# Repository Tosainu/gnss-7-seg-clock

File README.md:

# GNSS Seven-segment Clock

GNSS-powered, seven-segment table clock.

https://github.com/user-attachments/assets/9b2d0560-d879-4ddb-b99d-07a6e9839360

Full video: https://www.youtube.com/watch?v=Y1P_iDvq4bk

## Firmware

### Usage

Pre-build firmware files are available on the [release page](https://github.com/Tosainu/gnss-7-seg-clock/releases). Thanks to the RP2040 Bootrom, flashing the firmware requires no special tool. Connect the board to the PC using the USB-C cable, while holding the BOOT button (`SW2`). Once the `RPI-RP2` drive appears on the PC, copy `gnss-7-seg-clock.uf2` there. The board will automatically be rebooted as soon as it finishes writing to Flash.

- The board displays `--.--.--` until it obtains the time information.
- Press `SW3` to change the display contents:
    1. Time: `hh.mm.ss`
    2. Date: `YY.MM.DD`
    3. Configuring time zone (time offset): `[-]hh.mm`
        - `SW4`: + 30 min
        - `SW5`: - 30 min

### Build

The firmware is written in the [Rust][rust] programming language with the [Embassy][embassy] framework. In order to build the firmware, you first need to prepare the Rust toolchain. Please refer to the [official guide][rustup].

Next, install the linker helper [`flip-link`][flip-link]. Alternatively, remove [this line](https://github.com/Tosainu/gnss-7-seg-clock/blob/446c9426d9386b7eddf7218308c7567423a233c5/.cargo/config.toml#L11) to use the default linker.

    $ cargo install --locked flip-link

Lastly, run the command below to build the firmware. You can find the ELF file `./target/thumbv6m-none-eabi/release/gnss-7-seg-clock` afterward.

    $ cargo build --release

If the debug probe is attached to the board and [probe-rs][probe-rs] is installed on your PC, `cargo run` can be used to load firmware to the board.

    $ cargo run --release
    
    # to run test apps in crates/gnss-7-seg-clock/examples/
    $ cargo run --release --example gnss-uart-pipe

## Schematic and PCB

> [!IMPORTANT]
> I'm new to circuits and PCB designs. Any feedback and advice are welcome! (✿ゝ◡╹)ノ

I designed the Rev.A board with KiCad v8.0.8 (Linux/macOS) and their official libraries. You can find the KiCad project files in the [`hardware/`](./hardware/) directory. You can also find the rendered schematic (PDF) and Gerber files on the [release page](https://github.com/Tosainu/gnss-7-seg-clock/releases/tag/hardware%2Frev-a).

<sub>
Please do not take a close look at 43-44 pins of RP2040! (ignorable solder bridge)
</sub>

### Parts

> [!NOTE]
> Tolerances were set by just referring to several existing designs. Some of them might be insufficient or overkill.

| Reference | Value | Parts | Qty |
| --- | --- | --- | --: |
| `C1`, `C2`, `C4-C10`, `C14`, `C17-C19` | MLCC, 0.1uF, 10%, 6.3V, X5R, M1005 | | 13 |
| `C3`, `C11` | MLCC, 1uF, 20%, 6.3V, X5R, M1005 | | 2 |
| [`C12`, `C13`](#ldo-and-capacitors) | MLCC, 10uF, 10%, 6.3V, X7R, M2012 | | 2 |
| `C15`, `C16` | MLCC, 15pF, 5%, 50V, C0G/NP0, M1005 | | 2 |
| [`C20`](#rf-circuitry-for-max-m10s) | MLCC, 10000pF, 10%, 16V, X7R, M1005 | | 1 |
| [`C21`](#rf-circuitry-for-max-m10s) | MLCC, 47pF, 5%, 50V, C0G/NP0, M1005 | | 1 |
| [`D1`](#rf-circuitry-for-max-m10s) | Bidirectional TVS, M1005 | [Littelfuse PESD0402-140][PESD0402-140] | 1 |
| `D2-D7` | LED, M1005 | | 6 |
| `J1` | USB-C Receptacle | [GCT USB4105-GF-A](https://gct.co/connector/usb4105) | 1 |
| `J2` | SMA Receptacle, Edge Mount | [Molex 732511153][732511153] | 1 |
| `J3` | Pin header, 01x03, P2.54 mm | | 1 |
| [`L1`](#rf-circuitry-for-max-m10s) | Inductor, 27nH, 5%, M1005 | [Murata LQG15HS27NJ02D][LQG15HS27NJ02D] | 1 |
| [`R1-R3`](#driving-seven-segment-leds-with-fewer-pins) | Resistor, 2.2kOhm, 1%, 1/16W, M1005 | | 3 |
| `R4`, `R5`, `R12`, `R14-R16` | Resistor, 10kOhm, 1%, 1/16W, M1005 | | 6 |
| `R6`, `R7` | Resistor, 5.1kOhm, 1%, 1/16W, M1005 | | 2 |
| `R8`, `R9` | Resistor, 27Ohm, 1%, 1/16W, M1005 | | 2 |
| `R10`, `R13` | Resistor, 1kOhm, 1%, 1/16W, M1005 | | 2 |
| [`R11`](#rf-circuitry-for-max-m10s) | Resistor, 10Ohm, 5%, 1/4W, M1005 | | 1 |
| `R17-R22` | Resistor, 470Ohm, 1%, 1/16W, M1005 | | 6 |
| `SW1-SW5` | Tactile Switch | [C&K PTS810][PTS810] | 5 |
| [`U1-U6`](#seven-segment-leds) | 7-segment LED, Common-Anode, 3.81 mm | | 6 |
| [`U7-U9`](#driving-seven-segment-leds-with-fewer-pins) | 16-ch LED sink driver, SOIC-24W | [TI TLC5925IDWR][TLC5925] | 3 |
| `U10` | MCU | [Raspberry Pi RP2040][RP2040] | 1 |
| [`U11`](#ldo-and-capacitors) | LDO, 3.3V, 500 mA, SOT-23-5 | [TI TLV75533PDBVR][TLV755P] | 1 |
| `U12` | SQPI NOR Flash, 32M-bit, SOIC-8 | [Winbond W25Q32JVSS][W25Q32JV] | 1 |
| `U13` | GNSS Receiver | [u-blox MAX-M10S][MAX-M10] | 1 |
| `Y1` | Crystal, 12MHz | [Abracon ABM8-272-T3][ABM8-272-T3] | 1 |
| | GNSS Active Antenna | [u-blox ANN-MB5][ANN-MB5] | 1 |

### Seven-segment LEDs

`U1-U6` are seven-segment LEDs, the essential components in this design. While selecting them, I was surprised about the poor availability of seven-segment LEDs, especially the larger models (> 1″). I wanted to use [Kingbright SA15-11GWA][SA15-11GWA] initially. However, due to the availability and price, I selected [WENRUN LSD150BAG-101][LSD150BAG-101], even though I had to use a different store from other parts.

Unfortunately, LSD150BAG-101 is not a drop-in replacement for SA15-11GWA. They have a different pitch for the vertical direction: 40.64mm (SA15-11GWA) and 40.00mm (LSD150BAG-101). Since I wanted to have some flexibility in the design, I made the footprint that uses the oval pad so that can use both types of seven-segment LEDs.

The forward voltage also has to be taken into account for `U1-U6`. Vf should be smaller than the USB VBUS. For instance, high-luminance types are not suitable in general.

### Driving Seven-segment LEDs with Fewer Pins

`U7`, `U8`, and `U9` are 16-ch shift registers specialized for the LED, [TI TLC5925IDWR](TLC5925). Thanks to this three-cascading configuration, it can drive six seven-segment LEDs (48x LED segments) only by five pins.

TLC5925 determines the output currents based on an external resistor between the `R-EXT` pin and `GND`. `R1`, `R2`, and `R3` are the current-set resistors for `U7`, `U8`, and `U9` respectively. With the 2.2kOhm resistor, the output would be (1.21 / 2,200) \* 18  = 9.9mA.

### LDO and Capacitors

`U11` is the 3.3V LDO, [TI TLV75533PDBVR](TLV755P) (TLV755P-series). I'm hoping it works nicely with an AC adapter/wall charger as well as a PC because of its good PSRR in wide-range frequencies.

`C12` and `C13` are the input and output capacitors for the LDO. According to the datasheet, TLV755P requires a 1uF+ input capacitor and a 0.47uF+ output capacitor while considering the DC bias characteristics of a capacitor. Based on this, I selected 10uF/6.3V MLCC.

### RF Circuitry for MAX-M10S

[sparkfun/SparkFun\_u-blox\_MAX-M10S][SparkFun-MAX-M10S] is very good material as well as the MAX-M10S Integration manual. For the RF part, I imitated SparkFun's board and filled in parts values based on the reference design mentioned in the integration manual. Here are the parts correspondences between this board and the MAX-M10S reference design:

| This board | Reference design | Use |
| --- | --- | --- |
| `C20` | `C14` |  RF Bias-T Capacitor |
| `C21` | `C18` | DC Block Capacitor[^dc-block-cap] |
| `L1` | `L3` | RF Bias-T Inductor |
| `R11` | `R8` | Antenna supervisor current limiter/shunt resistor |

`D1` is the ESD-protection TVS which is only in the SparkFun's board. Since I have no confidence in finding compatible parts, I used the same TVS [Littelfuse PESD0402-140][PESD0402-140] in this design.

[^dc-block-cap]: Apparently, this capacitor can be removed as my design doesn't have an external SAW filter. The built-in DC-block capacitor of the module is sufficient.

## Special Thanks - PCBWay

I would like to say a special thank you to [PCBWay](https://www.pcbway.com/) for reaching out and sponsoring my project. As part of the sponsorship, I had the opportunity to try their PCBA service. Overall I am very satisfied with the service and quality of the PCBs. Especially,

- Swift and kind support
    - I was surprised that they reviewed my design files very quickly and gave me a reply after about an hour from the order.
- Numerous customization options for PCB manufacturing
- Help Center
    - There are how-to specialized for KiCad such as [_"How to Generate Gerber and Drill Files in KiCad 8.0?"_](https://www.pcbway.com/helpcenter/generate_gerber/Generate_Gerber_file_from_Kicad.html) and [_"Generate Position File Centroid File(pick place) in Kicad"_](https://www.pcbway.com/helpcenter/design_instruction/Generate_Position_File_in_Kicad.html). They were very helpful when I generate design files for the order.
- Quality of PCBs
    - The board has RP2040 which is the 0.20 mm pitch IC but there were no major issues. One thing to note is the soldermask color: green would be the only choice for such boards according to their explanations and the document [_"Soldermask Issues - Soldermask bridge"_](https://www.pcbway.com/helpcenter/soldermask_issues/Soldermask_bridge.html).

Note that I made some changes from the Rev.A design for this order, such as changing footprints to a non-HandSolder variant. If you're interested in about the design files I used to order, please refer to the [Rev.A2 release](https://github.com/Tosainu/gnss-7-seg-clock/releases/tag/hardware%2Frev-a2).

## License

The project is licensed under the [MIT](./LICENSE) license unless otherwise stated.

PCD design files, specifically the files under the [`hardware/`](./hardware/) directory are licensed under the [CC BY-SA 4.0](https://creativecommons.org/licenses/by-sa/4.0/) license. Please note that:
- Footprint files described below are made based on the [KiCad Footprint Libraries](https://gitlab.com/kicad/libraries/kicad-footprints) which is licensed under the [CC-BY-SA 4.0 license with exceptions](https://gitlab.com/kicad/libraries/kicad-footprints/-/blob/8.0.8/LICENSE.md?ref_type=tags).
    - [`Display_7Segment_1.5inch_P2.45mm.kicad_mod`](./hardware/gnss-7-seg-clock.pretty/Display_7Segment_1.5inch_P2.45mm.kicad_mod)
    - [`QFN-56-1EP_7x7mm_P0.4mm_EP3.2x3.2mm_HandSolder.kicad_mod`](./hardware/gnss-7-seg-clock.pretty/QFN-56-1EP_7x7mm_P0.4mm_EP3.2x3.2mm_HandSolder.kicad_mod)
    - [`SW_SPST_PTS810_HandSolder.kicad_mod`](./hardware/gnss-7-seg-clock.pretty/SW_SPST_PTS810_HandSolder.kicad_mod)
    - [`USB_C_Receptacle_GCT_USB4105-xx-A_16P_TopMnt_Horizontal_HandSolder.kicad_mod`](./hardware/gnss-7-seg-clock.pretty/USB_C_Receptacle_GCT_USB4105-xx-A_16P_TopMnt_Horizontal_HandSolder.kicad_mod)
- 3D model of ublox MAX module [`MAX (STEP-AP214).STEP`](./hardware/3d_models/MAX%20(STEP-AP214).STEP) is copied from [u-blox/3D-Step-Models-Library@92ce6ba0](https://github.com/u-blox/3D-Step-Models-Library/tree/92ce6ba04a1dacdbec4c5b9e0c032d87bb4d9fc0).

    > Copyright (C) u-blox
    >
    > u-blox reserves all rights in this deliverable (documentation, software, etc., hereafter “Deliverable”).
    >
    > u-blox grants you the right to use, copy, modify and distribute the Deliverable provided hereunder for any purpose without fee.
    >
    > THIS DELIVERABLE IS BEING PROVIDED "AS IS", WITHOUT ANY EXPRESS OR IMPLIED WARRANTY. IN PARTICULAR, NEITHER THE AUTHOR NOR U-BLOX MAKES ANY REPRESENTATION OR WARRANTY OF ANY KIND CONCERNING THE MERCHANTABILITY OF THIS DELIVERABLE OR ITS FITNESS FOR ANY PARTICULAR PURPOSE.
    >
    > In case you provide us a feedback or make a contribution in the form of a further development of the Deliverable (“Contribution”), u-blox will have the same rights as granted to you, namely to use, copy, modify and distribute the Contribution provided to us for any purpose without fee.

- Circuits around the MAX-M10S module on the schematic are made based on [sparkfun/SparkFun\_u-blox\_MAX-M10S][SparkFun-MAX-M10S] which is licensed under the [CC BY-SA 4.0](https://github.com/sparkfun/SparkFun_u-blox_MAX-M10S/blob/8e937406ba0f21e3afc8ca20ddeb06b088023951/LICENSE.md#hardware) license for the hardware part.

This project is inspired by [Kello version 4](http://kair.us/projects/clock/v4/index.html).

[rust]: https://www.rust-lang.org/
[rustup]: https://www.rust-lang.org/tools/install
[embassy]: https://embassy.dev/
[flip-link]: https://github.com/knurling-rs/flip-link
[probe-rs]: https://probe.rs/

[RP2040]: https://www.raspberrypi.com/products/rp2040/
[LQG15HS27NJ02D]: https://www.murata.com/en-global/products/productdetail?partno=LQG15HS27NJ02%23
[LSD150BAG-101]: https://www.tme.eu/en/details/lsd150bag-101/7-segment-led-displays/wenrun/lsd150bag-101-01/
[PESD0402-140]: https://www.littelfuse.com/products/overvoltage-protection/polymer-esd-suppressors/pesd-protection-device/pesd/pesd0402-140
[PTS810]: https://www.ckswitches.com/products/switches/product-details/Tactile/PTS810/
[TLC5925]: https://www.ti.com/product/TLC5925
[TLV755P]: https://www.ti.com/product/TLV755P
[W25Q32JV]: https://www.winbond.com/hq/product/code-storage-flash-memory/serial-nor-flash/?__locale=en&partNo=W25Q32JV
[732511153]: https://www.molex.com/en-us/products/part-detail/732511153
[USB4105]: https://gct.co/connector/usb4105
[ABM8-272-T3]: https://abracon.com/datasheets/ABM8-272-T3.pdf
[ANN-MB5]: https://www.u-blox.com/en/product/ann-mb5-antenna
[MAX-M10]: https://www.u-blox.com/en/product/max-m10-series
[SA15-11GWA]: https://www.kingbrightusa.com/product.asp?catalog_name=LED&product_id=SA15-11GWA

[SparkFun-MAX-M10S]: https://github.com/sparkfun/SparkFun_u-blox_MAX-M10S

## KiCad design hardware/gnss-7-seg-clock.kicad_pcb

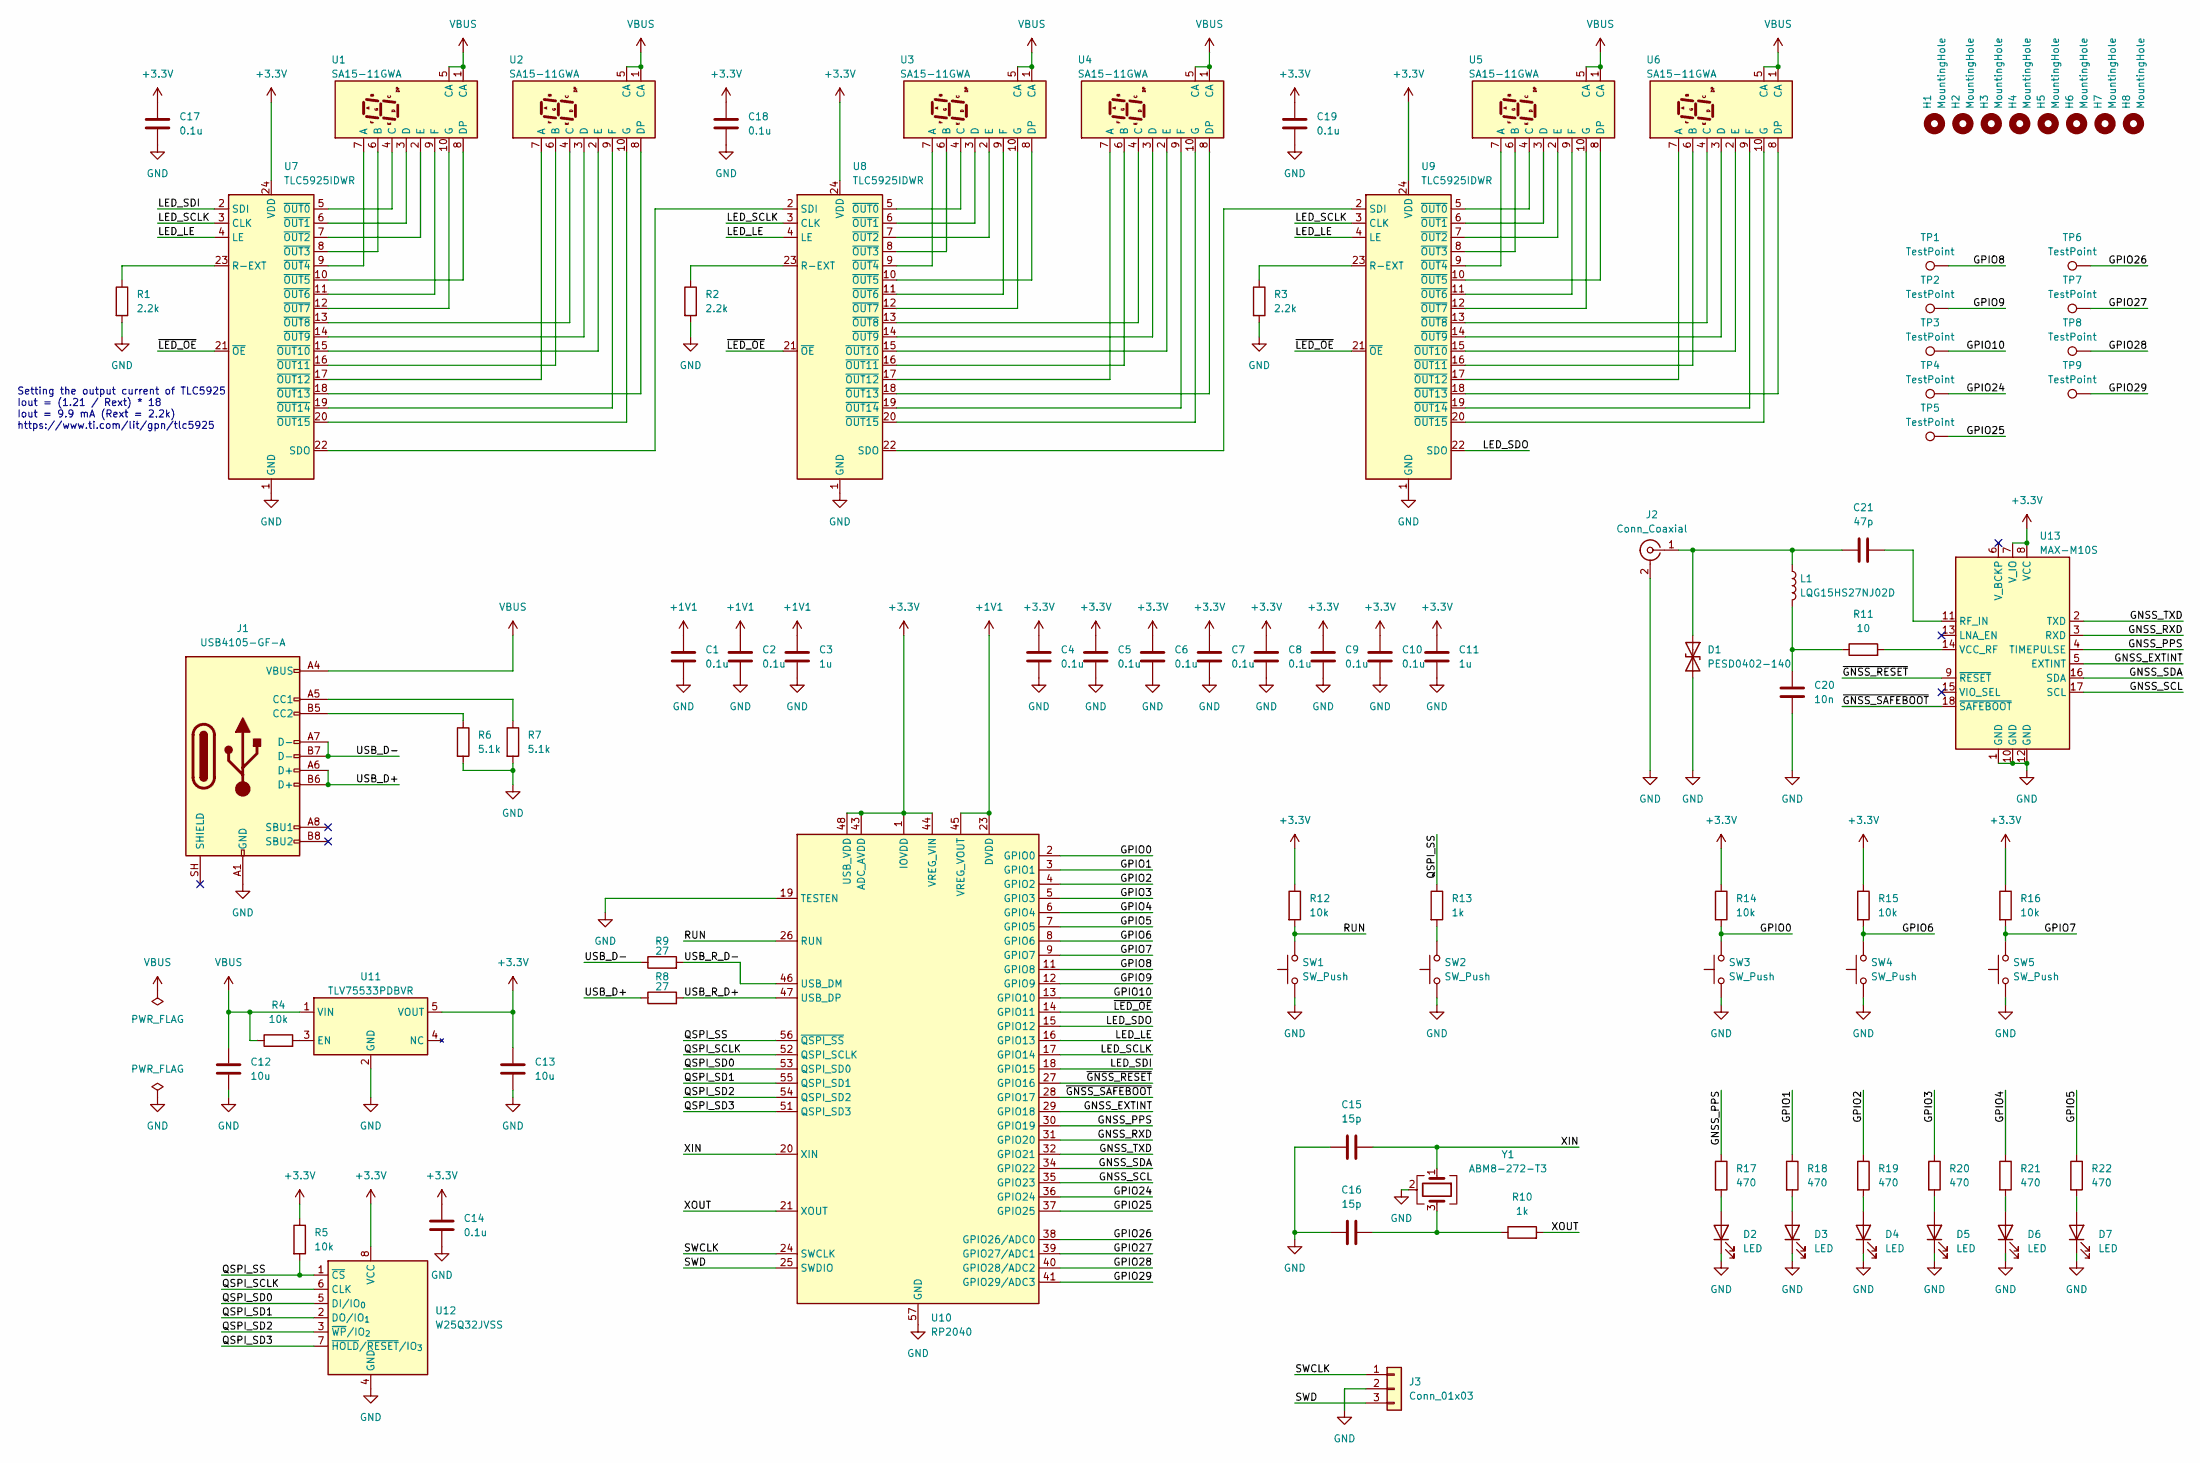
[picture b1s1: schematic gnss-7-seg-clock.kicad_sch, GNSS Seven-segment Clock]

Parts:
C1, C2, C4, C5, C6, C7, C8, C9, C10, C14, C17, C18, C19: 0.1u; C_0402_1005Metric_Pad0.74x0.62mm_HandSolder
C3, C11: 1u; C_0402_1005Metric_Pad0.74x0.62mm_HandSolder
C12, C13: 10u; C_0805_2012Metric_Pad1.18x1.45mm_HandSolder
C15, C16: 15p; C_0402_1005Metric_Pad0.74x0.62mm_HandSolder
C20: 10n; C_0402_1005Metric_Pad0.74x0.62mm_HandSolder
C21: 47p; C_0402_1005Metric_Pad0.74x0.62mm_HandSolder
D1: PESD0402-140; D_0402_1005Metric_Pad0.77x0.64mm_HandSolder
D2, D3, D4, D5, D6, D7: LED; LED_0402_1005Metric_Pad0.77x0.64mm_HandSolder
H1, H2, H3, H4, H5, H6, H7, H8: MountingHole; MountingHole_3.2mm_M3
J1: USB4105-GF-A; USB_C_Receptacle_GCT_USB4105-xx-A_16P_TopMnt_Horizontal_Han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
J2: Conn_Coaxial; SMA_Molex_73251-1153_EdgeMount_Horizontal
J3: Conn_01x03; PinHeader_1x03_P2.54mm_Vertical
L1: LQG15HS27NJ02D; L_0402_1005Metric_Pad0.77x0.64mm_HandSolder
R1, R2, R3: 2.2k; R_0402_1005Metric_Pad0.72x0.64mm_HandSolder
R4, R5, R12, R14, R15, R16: 10k; R_0402_1005Metric_Pad0.72x0.64mm_HandSolder
R6, R7: 5.1k; R_0402_1005Metric_Pad0.72x0.64mm_HandSolder
R8, R9: 27; R_0402_1005Metric_Pad0.72x0.64mm_HandSolder
R10, R13: 1k; R_0402_1005Metric_Pad0.72x0.64mm_HandSolder
R11: 10; R_0402_1005Metric_Pad0.72x0.64mm_HandSolder
R17, R18, R19, R20, R21, R22: 470; R_0402_1005Metric_Pad0.72x0.64mm_HandSolder
SW1, SW2, SW3, SW4, SW5: SW_Push; SW_SPST_PTS810_HandSolder
TP1, TP2, TP3, TP4, TP5, TP6, TP7, TP8, TP9: TestPoint; TestPoint_Pad_1.0x1.0mm
U1, U2, U3, U4, U5, U6: SA15-11GWA; Display_7Segment_1.5inch_P2.45mm
U7, U8, U9: TLC5925IDWR; SOIC-24W_7.5x15.4mm_P1.27mm
U10: RP2040; QFN-56-1EP_7x7mm_P0.4mm_EP3.2x3.2mm
U11: TLV75533PDBVR; TSOT-23-5_HandSoldering
U12: W25Q32JVSS; SOIC-8_5.3x5.3mm_P1.27mm
U13: MAX-M10S
Y1: ABM8-272-T3; Crystal_SMD_3225-4Pin_3.2x2.5mm_HandSoldering

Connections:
+1V1: C1.1, C2.1, C3.1, U10.23 (DVDD), U10.45 (VREG_VOUT), U10.50 (DVDD)
+3.3V: C4.1, C5.1, C6.1, C7.1, C8.1, C9.1, C10.1, C11.1, C13.1, C14.1, C17.1, C18.1, C19.1, R5.1, R12.1, R14.1, R15.1, R16.1, U7.24 (VDD), U8.24 (VDD), U9.24 (VDD), U10.1 (IOVDD), U10.10 (IOVDD), U10.22 (IOVDD), U10.33 (IOVDD), U10.42 (IOVDD), U10.43 (ADC_AVDD), U10.44 (VREG_VIN), U10.48 (USB_VDD), U10.49 (IOVDD), U11.5 (VOUT), U12.8 (VCC), U13.7 (V_IO), U13.8 (VCC)
/GNSS_EXTINT: U10.29 (GPIO18), U13.5 (EXTINT)
/GNSS_PPS: R17.1, U10.30 (GPIO19), U13.4 (TIMEPULSE)
/GNSS_RXD: U10.31 (GPIO20), U13.3 (RXD)
/GNSS_SCL: U10.35 (GPIO23), U13.17 (SCL)
/GNSS_SDA: U10.34 (GPIO22), U13.16 (SDA)
/GNSS_TXD: U10.32 (GPIO21), U13.2 (TXD)
/GPIO0: R14.2, SW3.2, U10.2 (GPIO0)
/GPIO1: R18.1, U10.3 (GPIO1)
/GPIO2: R19.1, U10.4 (GPIO2)
/GPIO3: R20.1, U10.5 (GPIO3)
/GPIO4: R21.1, U10.6 (GPIO4)
/GPIO5: R22.1, U10.7 (GPIO5)
/GPIO6: R15.2, SW4.2, U10.8 (GPIO6)
/GPIO7: R16.2, SW5.2, U10.9 (GPIO7)
/GPIO8: TP1.1, U10.11 (GPIO8)
/GPIO9: TP2.1, U10.12 (GPIO9)
/GPIO10: TP3.1, U10.13 (GPIO10)
/GPIO24: TP4.1, U10.36 (GPIO24)
/GPIO25: TP5.1, U10.37 (GPIO25)
/GPIO26: TP6.1, U10.38 (GPIO26/ADC0)
/GPIO27: TP7.1, U10.39 (GPIO27/ADC1)
/GPIO28: TP8.1, U10.40 (GPIO28/ADC2)
/GPIO29: TP9.1, U10.41 (GPIO29/ADC3)
/LED_LE: U7.4 (LE), U8.4 (LE), U9.4 (LE), U10.16 (GPIO13)
/LED_SCLK: U7.3 (CLK), U8.3 (CLK), U9.3 (CLK), U10.17 (GPIO14)
/LED_SDI: U7.2 (SDI), U10.18 (GPIO15)
/LED_SDO: U9.22 (SDO), U10.15 (GPIO12)
/QSPI_SCLK: U10.52 (QSPI_SCLK), U12.6 (CLK)
/QSPI_SD0: U10.53 (QSPI_SD0), U12.5 (DI/IO_{0})
/QSPI_SD1: U10.55 (QSPI_SD1), U12.2 (DO/IO_{1})
/QSPI_SD2: U10.54 (QSPI_SD2), U12.3 (~WP/IO_{2})
/QSPI_SD3: U10.51 (QSPI_SD3), U12.7 (~HOLD/~RESET/IO_{3})
/QSPI_SS: R5.2, R13.1, U10.56 (~QSPI_SS), U12.1 (~CS)
/RUN: R12.2, SW1.2, U10.26 (RUN)
/SWCLK: J3.1, U10.24 (SWCLK)
/SWD: J3.3, U10.25 (SWDIO)
/USB_D+: J1.A6 (D+), J1.B6 (D+), R8.1
/USB_D-: J1.A7 (D-), J1.B7 (D-), R9.1
/USB_R_D+: R8.2, U10.47 (USB_DP)
/USB_R_D-: R9.2, U10.46 (USB_DM)
/XIN: C15.2, U10.20 (XIN), Y1.1
/XOUT: R10.2, U10.21 (XOUT)
/~GNSS_RESET: U10.27 (GPIO16), U13.9 (~RESET)
/~GNSS_SAFEBOOT: U10.28 (GPIO17), U13.18 (~SAFEBOOT)
/~LED_OE: U7.21 (~OE), U8.21 (~OE), U9.21 (~OE), U10.14 (GPIO11)
GND: C1.2, C2.2, C3.2, C4.2, C5.2, C6.2, C7.2, C8.2, C9.2, C10.2, C11.2, C12.2, C13.2, C14.2, C15.1, C16.1, C17.2, C18.2, C19.2, C20.2, D1.2 (A2), D2.1 (K), D3.1 (K), D4.1 (K), D5.1 (K), D6.1 (K), D7.1 (K), J1.A1 (GND), J1.A12 (GND), J1.B1 (GND), J1.B12 (GND), J2.2 (Ext), J3.2, R1.2, R2.2, R3.2, R6.2, R7.2, SW1.1, SW2.1, SW3.1, SW4.1, SW5.1, U7.1 (GND), U8.1 (GND), U9.1 (GND), U10.19 (TESTEN), U10.57 (GND), U11.2 (GND), U12.4 (GND), U13.1 (GND), U13.10 (GND), U13.12 (GND), Y1.2 (G), Y1.4 (G)
unnamed: C16.2, R10.1, Y1.3
unnamed: C20.1, L1.2, R11.1
unnamed: C21.1, D1.1 (A1), J2.1 (In), L1.1
unnamed: D2.2 (A), R17.2
unnamed: D3.2 (A), R18.2
unnamed: D4.2 (A), R19.2
unnamed: D5.2 (A), R20.2
unnamed: D6.2 (A), R21.2
unnamed: D7.2 (A), R22.2
unnamed: J1.A5 (CC1), R7.1
unnamed: J1.B5 (CC2), R6.1
unnamed: R13.2, SW2.2
unnamed: U1.7 (A), U7.9 (~OUT4)
unnamed: U1.6 (B), U7.8 (~OUT3)
unnamed: U1.4 (C), U7.5 (~OUT0)
unnamed: U1.3 (D), U7.6 (~OUT1)
unnamed: U1.8 (DP), U7.10 (~OUT5)
unnamed: U1.2 (E), U7.7 (~OUT2)
unnamed: U1.9 (F), U7.11 (~OUT6)
unnamed: U1.10 (G), U7.12 (~OUT7)
unnamed: U2.7 (A), U7.17 (~OUT12)
unnamed: U2.6 (B), U7.16 (~OUT11)
unnamed: U2.4 (C), U7.13 (~OUT8)
unnamed: U2.3 (D), U7.14 (~OUT9)
unnamed: U2.8 (DP), U7.18 (~OUT13)
unnamed: U2.2 (E), U7.15 (~OUT10)
unnamed: U2.9 (F), U7.19 (~OUT14)
unnamed: U2.10 (G), U7.20 (~OUT15)
unnamed: U3.7 (A), U8.9 (~OUT4)
unnamed: U3.6 (B), U8.8 (~OUT3)
unnamed: U3.4 (C), U8.5 (~OUT0)
unnamed: U3.3 (D), U8.6 (~OUT1)
unnamed: U3.8 (DP), U8.10 (~OUT5)
unnamed: U3.2 (E), U8.7 (~OUT2)
unnamed: U3.9 (F), U8.11 (~OUT6)
unnamed: U3.10 (G), U8.12 (~OUT7)
unnamed: U4.7 (A), U8.17 (~OUT12)
unnamed: U4.6 (B), U8.16 (~OUT11)
unnamed: U4.4 (C), U8.13 (~OUT8)
unnamed: U4.3 (D), U8.14 (~OUT9)
unnamed: U4.8 (DP), U8.18 (~OUT13)
unnamed: U4.2 (E), U8.15 (~OUT10)
unnamed: U4.9 (F), U8.19 (~OUT14)
unnamed: U4.10 (G), U8.20 (~OUT15)
unnamed: U5.7 (A), U9.9 (~OUT4)
unnamed: U5.6 (B), U9.8 (~OUT3)
unnamed: U5.4 (C), U9.5 (~OUT0)
unnamed: U5.3 (D), U9.6 (~OUT1)
unnamed: U5.8 (DP), U9.10 (~OUT5)
unnamed: U5.2 (E), U9.7 (~OUT2)
unnamed: U5.9 (F), U9.11 (~OUT6)
unnamed: U5.10 (G), U9.12 (~OUT7)
unnamed: U6.7 (A), U9.17 (~OUT12)
unnamed: U6.6 (B), U9.16 (~OUT11)
unnamed: U6.4 (C), U9.13 (~OUT8)
unnamed: U6.3 (D), U9.14 (~OUT9)
unnamed: U6.8 (DP), U9.18 (~OUT13)
unnamed: U6.2 (E), U9.15 (~OUT10)
unnamed: U6.9 (F), U9.19 (~OUT14)
unnamed: U6.10 (G), U9.20 (~OUT15)
unnamed: R1.1, U7.23 (R-EXT)
unnamed: U7.22 (SDO), U8.2 (SDI)
unnamed: R2.1, U8.23 (R-EXT)
unnamed: U8.22 (SDO), U9.2 (SDI)
unnamed: R3.1, U9.23 (R-EXT)
unnamed: R4.2, U11.3 (EN)
unnamed: C21.2, U13.11 (RF_IN)
unnamed: R11.2, U13.14 (VCC_RF)
VBUS: C12.1, J1.A4 (VBUS), J1.A9 (VBUS), J1.B4 (VBUS), J1.B9 (VBUS), R4.1, U1.1 (CA), U1.5 (CA), U2.1 (CA), U2.5 (CA), U3.1 (CA), U3.5 (CA), U4.1 (CA), U4.5 (CA), U5.1 (CA), U5.5 (CA), U6.1 (CA), U6.5 (CA), U11.1 (VIN)

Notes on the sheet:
Setting the output current of TLC5925 Iout = (1.21 / Rext) * 18 Iout = 9.9 mA (Rext = 2.2k) https://www.ti.com/lit/gpn/tlc5925

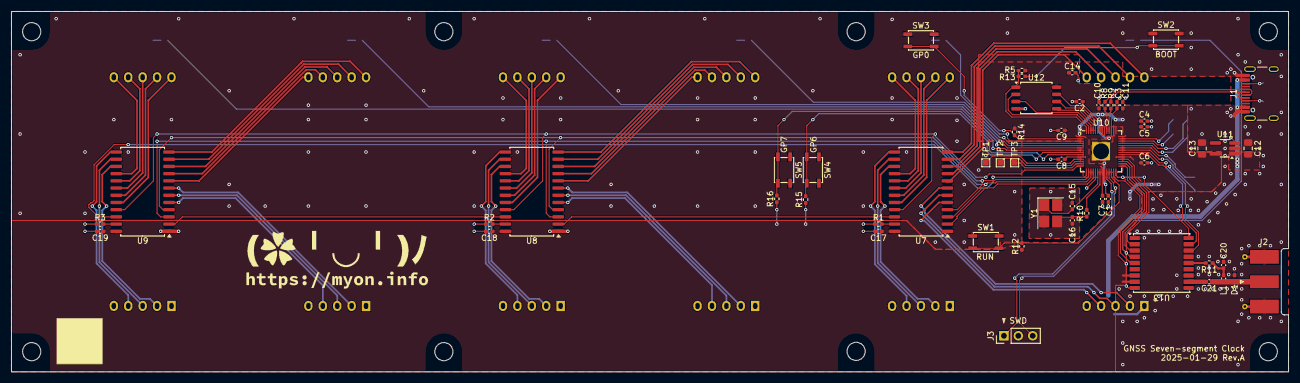
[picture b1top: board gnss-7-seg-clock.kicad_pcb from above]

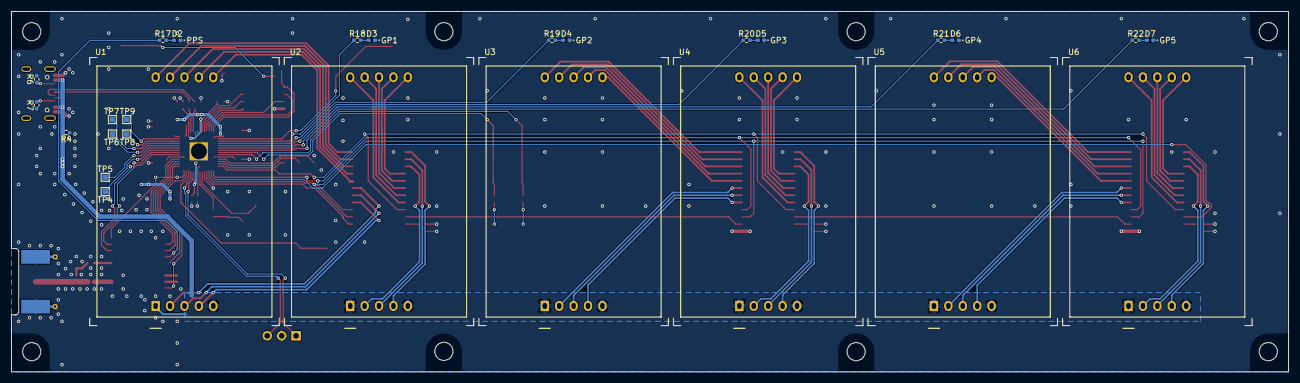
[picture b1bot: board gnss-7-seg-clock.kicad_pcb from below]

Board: 2 copper layers, 225.0 x 63.5 mm, 90 parts (27 on the bottom side), 117 nets.

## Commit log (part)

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2025-01-29 Hardware Rev.A
2025-02-09 Add led checkout program
2025-02-12 Add MAX-M10S I2C checkout program
2025-02-15 Use `nmea` crate to parse NMEA sentences
2025-02-21 Rust 2024
2025-02-23 Add `DisplayMode::ConfigTimeZone` for setting time zone
2025-03-09 Bump chrono from 0.4.39 to 0.4.40
    Bumps [chrono](https://github.com/chronotope/chrono) from 0.4.39 to 0.4.40.
    - [Release notes](https://github.com/chronotope/chrono/releases)
    - [Changelog](https://github.com/chronotope/chrono/blob/main/CHANGELOG.md)
    - [Commits](https://github.com/chronotope/chrono/compare/v0.4.39...v0.4.40)
    ---
    updated-dependencies:
2025-03-09 Bump softprops/action-gh-release (#4)
    Bumps [softprops/action-gh-release](https://github.com/softprops/action-gh-release) from daffc988f27cd136af07d2cdcbf7ceae2993875d to 670eb2f21a607fad397653d7e45de8f17ade7cc4.
    - [Release notes](https://github.com/softprops/action-gh-release/releases)
    - [Changelog](https://github.com/softprops/action-gh-release/blob/master/CHANGELOG.md)
    - [Commits](https://github.com/softprops/action-gh-release/compare/daffc988f27cd136af07d2cdcbf7ceae2993875d...670eb2f21a607fad397653d7e45de8f17ade7cc4)
    ---
    updated-dependencies:
2025-03-29 Update W25Q32JVSS footprint
    see also: https://gitlab.com/kicad/libraries/kicad-footprint-generator/-/merge_requests/1384
2025-04-02 Bump actions/download-artifact from 4.1.9 to 4.2.1 (#7)
    Bumps [actions/download-artifact](https://github.com/actions/download-artifact) from 4.1.9 to 4.2.1.
    - [Release notes](https://github.com/actions/download-artifact/releases)
    - [Commits](https://github.com/actions/download-artifact/compare/v4.1.9...v4.2.1)
    ---
    updated-dependencies:
    - dependency-name: actions/download-artifact
2025-04-02 Bump defmt from 0.3.10 to 1.0.1
    Bumps [defmt](https://github.com/knurling-rs/defmt) from 0.3.10 to 1.0.1.
    - [Release notes](https://github.com/knurling-rs/defmt/releases)
    - [Changelog](https://github.com/knurling-rs/defmt/blob/main/CHANGELOG.md)
    - [Commits](https://github.com/knurling-rs/defmt/commits)
    ---
    updated-dependencies:
2025-04-02 Bump defmt-rtt from 0.4.1 to 0.4.2 (#12)
    Bumps [defmt-rtt](https://github.com/knurling-rs/defmt) from 0.4.1 to 0.4.2.
    - [Release notes](https://github.com/knurling-rs/defmt/releases)
    - [Changelog](https://github.com/knurling-rs/defmt/blob/main/CHANGELOG.md)
    - [Commits](https://github.com/knurling-rs/defmt/commits)
    ---
    updated-dependencies:
2025-05-02 Bump chrono from 0.4.40 to 0.4.41 (#14)
    Bumps [chrono](https://github.com/chronotope/chrono) from 0.4.40 to 0.4.41.
    - [Release notes](https://github.com/chronotope/chrono/releases)
    - [Changelog](https://github.com/chronotope/chrono/blob/main/CHANGELOG.md)
    - [Commits](https://github.com/chronotope/chrono/compare/v0.4.40...v0.4.41)
    ---
    updated-dependencies:
2025-05-03 Fix cloppy
2025-07-01 Bump static_cell from 2.1.0 to 2.1.1 (#21)
    Bumps [static_cell](https://github.com/embassy-rs/static-cell) from 2.1.0 to 2.1.1.
    - [Changelog](https://github.com/embassy-rs/static-cell/blob/main/CHANGELOG.md)
    - [Commits](https://github.com/embassy-rs/static-cell/compare/v2.1.0...v2.1.1)
    ---
    updated-dependencies:
    - dependency-name: static_cell
2025-07-02 Cache the latest time
    This fixes regressin introduced in b24db0d2412d50fd361581d2e64102bfcc1be36a
2025-07-05 Add `docker-bake.hcl`
2025-08-11 Rework kicad CI
2025-08-12 Bump actions/download-artifact from 4.3.0 to 5.0.0 (#29)
    Bumps [actions/download-artifact](https://github.com/actions/download-artifact) from 4.3.0 to 5.0.0.
    - [Release notes](https://github.com/actions/download-artifact/releases)
    - [Commits](https://github.com/actions/download-artifact/compare/v4.3.0...v5.0.0)
    ---
    updated-dependencies:
    - dependency-name: actions/download-artifact
2025-09-03 Bump actions/checkout from 4.2.2 to 5.0.0 (#32)
    Bumps [actions/checkout](https://github.com/actions/checkout) from 4.2.2 to 5.0.0.
    - [Release notes](https://github.com/actions/checkout/releases)
    - [Changelog](https://github.com/actions/checkout/blob/main/CHANGELOG.md)
    - [Commits](https://github.com/actions/checkout/compare/v4.2.2...v5.0.0)
    ---
    updated-dependencies:
2025-10-01 Bump serde from 1.0.219 to 1.0.228
    Bumps [serde](https://github.com/serde-rs/serde) from 1.0.219 to 1.0.228.
    - [Release notes](https://github.com/serde-rs/serde/releases)
    - [Commits](https://github.com/serde-rs/serde/compare/v1.0.219...v1.0.228)
    ---
    updated-dependencies:
    - dependency-name: serde
2025-11-01 Bump softprops/action-gh-release
    Bumps [softprops/action-gh-release](https://github.com/softprops/action-gh-release) from 97d42c1b50f585f357413698aa1b779307aa0d52 to 0adea5aa98b89355a3ff602e3f2d18bc4d77e7aa.
    - [Release notes](https://github.com/softprops/action-gh-release/releases)
    - [Changelog](https://github.com/softprops/action-gh-release/blob/master/CHANGELOG.md)
    - [Commits](https://github.com/softprops/action-gh-release/compare/97d42c1b50f585f357413698aa1b779307aa0d52...0adea5aa98b89355a3ff602e3f2d18bc4d77e7aa)
    ---
    updated-dependencies:
2025-11-02 Bump softprops/action-gh-release (#37)
    Bumps [softprops/action-gh-release](https://github.com/softprops/action-gh-release) from 97d42c1b50f585f357413698aa1b779307aa0d52 to 0adea5aa98b89355a3ff602e3f2d18bc4d77e7aa.
    - [Release notes](https://github.com/softprops/action-gh-release/releases)
    - [Changelog](https://github.com/softprops/action-gh-release/blob/master/CHANGELOG.md)
    - [Commits](https://github.com/softprops/action-gh-release/compare/97d42c1b50f585f357413698aa1b779307aa0d52...0adea5aa98b89355a3ff602e3f2d18bc4d77e7aa)
    ---
    updated-dependencies:
2025-11-02 Bump panic-probe from 0.3.2 to 1.0.0 (#43)
    Bumps [panic-probe](https://github.com/knurling-rs/defmt) from 0.3.2 to 1.0.0.
    - [Release notes](https://github.com/knurling-rs/defmt/releases)
    - [Changelog](https://github.com/knurling-rs/defmt/blob/main/CHANGELOG.md)
    - [Commits](https://github.com/knurling-rs/defmt/compare/panic-probe-v0.3.2...defmt-v1.0.0)
    ---
    updated-dependencies:
2025-11-02 Bump embassy-rp from 0.3.1 to 0.7.0
    Bumps [embassy-rp](https://github.com/embassy-rs/embassy) from 0.3.1 to 0.7.0.
    - [Changelog](https://github.com/embassy-rs/embassy/blob/main/RELEASE.md)
    - [Commits](https://github.com/embassy-rs/embassy/compare/embassy-rp-v0.3.1...embassy-rp-v0.7.0)
    ---
    updated-dependencies:
    - dependency-name: embassy-rp
2025-12-01 Bump docker/bake-action from 6.9.0 to 6.10.0
    Bumps [docker/bake-action](https://github.com/docker/bake-action) from 6.9.0 to 6.10.0.
    - [Release notes](https://github.com/docker/bake-action/releases)
    - [Commits](https://github.com/docker/bake-action/compare/v6.9.0...v6.10.0)
    ---
    updated-dependencies:
    - dependency-name: docker/bake-action
2025-12-02 Bump softprops/action-gh-release (#52)
    Bumps [softprops/action-gh-release](https://github.com/softprops/action-gh-release) from 0adea5aa98b89355a3ff602e3f2d18bc4d77e7aa to a06a81a03ee405af7f2048a818ed3f03bbf83c7b.
    - [Release notes](https://github.com/softprops/action-gh-release/releases)
    - [Changelog](https://github.com/softprops/action-gh-release/blob/master/CHANGELOG.md)
    - [Commits](https://github.com/softprops/action-gh-release/compare/0adea5aa98b89355a3ff602e3f2d18bc4d77e7aa...a06a81a03ee405af7f2048a818ed3f03bbf83c7b)
    ---
    updated-dependencies:
2026-01-01 Bump actions/download-artifact from 6.0.0 to 7.0.0
    Bumps [actions/download-artifact](https://github.com/actions/download-artifact) from 6.0.0 to 7.0.0.
    - [Release notes](https://github.com/actions/download-artifact/releases)
    - [Commits](https://github.com/actions/download-artifact/compare/v6.0.0...v7.0.0)
    ---
    updated-dependencies:
    - dependency-name: actions/download-artifact
2026-01-10 Bump portable-atomic from 1.11.1 to 1.13.0 (#56)
    Bumps [portable-atomic](https://github.com/taiki-e/portable-atomic) from 1.11.1 to 1.13.0.
    - [Release notes](https://github.com/taiki-e/portable-atomic/releases)
    - [Changelog](https://github.com/taiki-e/portable-atomic/blob/main/CHANGELOG.md)
    - [Commits](https://github.com/taiki-e/portable-atomic/compare/v1.11.1...v1.13.0)
    ---
    updated-dependencies:
2026-01-17 Use ubx library in gnss-7-seg-clock
2026-02-02 Bump actions/checkout from 6.0.1 to 6.0.2 (#59)
    Bumps [actions/checkout](https://github.com/actions/checkout) from 6.0.1 to 6.0.2.
    - [Release notes](https://github.com/actions/checkout/releases)
    - [Changelog](https://github.com/actions/checkout/blob/main/CHANGELOG.md)
    - [Commits](https://github.com/actions/checkout/compare/v6.0.1...v6.0.2)
    ---
    updated-dependencies:
2026-02-28 fixup! use ubx
2026-03-02 Bump actions/download-artifact from 7.0.0 to 8.0.0 (#64)
    Bumps [actions/download-artifact](https://github.com/actions/download-artifact) from 7.0.0 to 8.0.0.
    - [Release notes](https://github.com/actions/download-artifact/releases)
    - [Commits](https://github.com/actions/download-artifact/compare/v7.0.0...v8.0.0)
    ---
    updated-dependencies:
    - dependency-name: actions/download-artifact
2026-04-02 Bump embassy-sync from 0.7.2 to 0.8.0
    Bumps [embassy-sync](https://github.com/embassy-rs/embassy) from 0.7.2 to 0.8.0.
    - [Changelog](https://github.com/embassy-rs/embassy/blob/main/RELEASE.md)
    - [Commits](https://github.com/embassy-rs/embassy/compare/embassy-sync-v0.7.2...embassy-sync-v0.8.0)
    ---
    updated-dependencies:
    - dependency-name: embassy-sync
2026-04-03 Bump softprops/action-gh-release from 2.5.0 to 2.6.1 (#68)
    * Bump softprops/action-gh-release from 2.5.0 to 2.6.1
    Bumps [softprops/action-gh-release](https://github.com/softprops/action-gh-release) from 2.5.0 to 2.6.1.
    - [Release notes](https://github.com/softprops/action-gh-release/releases)
    - [Changelog](https://github.com/softprops/action-gh-release/blob/master/CHANGELOG.md)
    - [Commits](https://github.com/softprops/action-gh-release/compare/a06a81a03ee405af7f2048a818ed3f03bbf83c7b...153bb8e04406b158c6c84fc1615b65b24149a1fe)
    ---
2026-04-03 Migrate embassy-rp 0.10.0
2026-04-03 Bump embassy-executor from 0.9.1 to 0.10.0 (#75)
2026-05-01 Bump actions/upload-artifact from 7.0.0 to 7.0.1
    Bumps [actions/upload-artifact](https://github.com/actions/upload-artifact) from 7.0.0 to 7.0.1.
    - [Release notes](https://github.com/actions/upload-artifact/releases)
    - [Commits](https://github.com/actions/upload-artifact/compare/v7.0.0...v7.0.1)
    ---
    updated-dependencies:
    - dependency-name: actions/upload-artifact
2026-05-03 Bump kicad/kicad from 10.0.0 to 10.0.1 (#80)
    Bumps [kicad/kicad](https://gitlab.com/kicad/kicad-ci/kicad-cli-docker) from 10.0.0 to 10.0.1.
    - [Commits](https://gitlab.com/kicad/kicad-ci/kicad-cli-docker/commits/main)
    ---
    updated-dependencies:
    - dependency-name: kicad/kicad
    dependency-version: 10.0.1
2026-06-04 Bump actions/checkout from 6.0.2 to 6.0.3 (#81)
    Bumps [actions/checkout](https://github.com/actions/checkout) from 6.0.2 to 6.0.3.
    - [Release notes](https://github.com/actions/checkout/releases)
    - [Changelog](https://github.com/actions/checkout/blob/main/CHANGELOG.md)
    - [Commits](https://github.com/actions/checkout/compare/v6.0.2...v6.0.3)
    ---
    updated-dependencies:
